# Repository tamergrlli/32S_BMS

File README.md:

# 32S BMS

A battery management system board for **16S to 32S** packs, built around two
stacked **TI BQ76952** monitors and an **STM32G0B1** microcontroller. Designed in
KiCad 10.

| | |
|---|---|
| Cell count | 16S to 32S (2 × BQ76952, up to 16 cells each) |
| Balancing | 32 external MOSFET balancing channels |
| Supply | 12 V nominal (see [Power](#power)) |
| Interfaces | CAN, 4 high-side outputs, 6 configurable inputs |
| Board | 90 × 100 mm, 4 copper layers, 1.6 mm |
| Parts | 413 footprints |
| Revision | V0.1 |

## Features

### Cell monitoring and balancing
- Two BQ76952 monitors (`bq76952_TOP` / `bq76952_BOTTOM`) stacked to cover up to
  32 cells. The cell count is configurable between 16S and 32S.
- 32 external balancing channels (AO3416 MOSFETs with 2512 bleed resistors) with
  zener gate protection.
- Cell sense inputs on two Molex Micro-Fit 3.0 2×10 connectors.

### Isolation
- Each monitor has its own isolated link to the MCU. An ISO1644 carries I²C, ALERT
  and SHUT, and a PC817 optocoupler drives WAKE.

### Inputs
- 6 input channels on one connector, multiplexed through a 74HC4051 into a single
  MCU ADC channel.
- Each channel has a 4.7 kΩ series resistor, a 10 kΩ pull-down and a 100 nF filter
  capacitor. The connector also provides a 3.3 V pin through a 47 Ω resistor.
- Because of this structure, the same input can read either an analog or a digital
  signal:
  - **NTC thermistor** between the 3.3 V pin and the input forms a divider with
    the on-board resistors.
  - **Button or switch** to 3.3 V reads high when closed and is held low by the
    pull-down when open.
  - **Analog voltage** up to about 4.8 V full scale, set by the 4.7 k / 10 k
    divider.
- On-board NTC for board temperature.

### Always-on operation and sleep on command
- The BMS runs continuously and enters sleep mode only on command, for example
  from a CAN message.
- A TPL5010 nano-power timer acts as an external watchdog. The MCU acknowledges it
  periodically, and if the firmware hangs, the TPL5010 resets the MCU. The reset
  output reaches NRST through a jumper, so the watchdog can be disabled.
- In sleep mode, the MCU can put each BQ76952 into SHUTDOWN and the CAN transceiver
  into standby. Wake sources:
  - CAN bus activity
  - a push button, through the TPL5010 manual-reset input
  - a BQ76952 ALERT

### Communication and outputs
- CAN bus with a TJA1042T/3 transceiver, TDK ACT45B common-mode choke and
  PESD1CAN ESD protection. 120 Ω termination is selectable by jumper.
- 4 high-side switched outputs (Infineon BTS724G) at supply voltage, with
  flyback diodes and status feedback to the MCU.

### MCU and peripherals
- STM32G0B1RE with an external main crystal and a 32.768 kHz RTC crystal. The
  RTC is backed up by a CR1220 coin cell.
- W25Q32 SPI flash (32 Mbit) for data logging.
- SWD header, two status LEDs, a buzzer and a push button.

### Power
- 12 V input, protected by:
  - a fuse
  - an SS34 series diode for reverse polarity on the logic supply
  - an SMAJ15CA TVS diode
  - a P-MOSFET with zener-clamped gate for reverse polarity on the output stage
- A TPS54302 buck converter makes 5 V, and an AP2112K LDO makes 3.3 V.
- **Supply range:** 12 V nominal.
  - The upper limit is set by the SMAJ15CA TVS: 15 V standoff, about 16.7 V
    breakdown.
  - At the low end, the 5 V buck plus the series diode drop need roughly 6–7 V.
  - The TPS54302 itself accepts 4.5–28 V, so the input protection is what limits
    the range.

## Firmware

Firmware is under development and will be published in this repository as it
progresses.

## Gallery

| Top | Bottom |
|---|---|
|  |  |

## Repository layout

```
32s_bms/        KiCad project (schematic sheets: POWER, IN_OUT, MCU, bq76952)
32s_bms_lib/    Every non-standard part used by the design
  symbols/      Custom schematic symbols
  footprints/   Custom footprint libraries (.pretty)
  3dmodels/     STEP models for connectors and custom parts
32s_gerber/     Gerber and drill files (exported 2026-10-12)
32s_pdf/        Schematic PDF
docs/           Renders
```

## Opening the project

1. Install [KiCad 10](https://www.kicad.org/download/).
2. Clone the repository and open `32s_bms/32s_bms.kicad_pro`.

All custom symbols, footprints and 3D models are included, and the project
library tables use `${KIPRJMOD}`-relative paths. You don't need to configure any
libraries. Everything else comes from KiCad's standard libraries.

## Notes

- This is revision V0.1, shared as a design reference. Battery packs at this
  series count carry hazardous voltages. Review and test the design yourself
  before using it with real cells.
- Third-party 3D models (Molex, JST, TDK, Panasonic and others) are the property
  of their manufacturers and are included only so the 3D view renders correctly.

## License

The design files are released under the [MIT License](LICENSE). Third-party 3D
models in `32s_bms_lib/3dmodels/` are not covered by this license and remain under
their manufacturers' terms.

## Author

Tamer Gürelli

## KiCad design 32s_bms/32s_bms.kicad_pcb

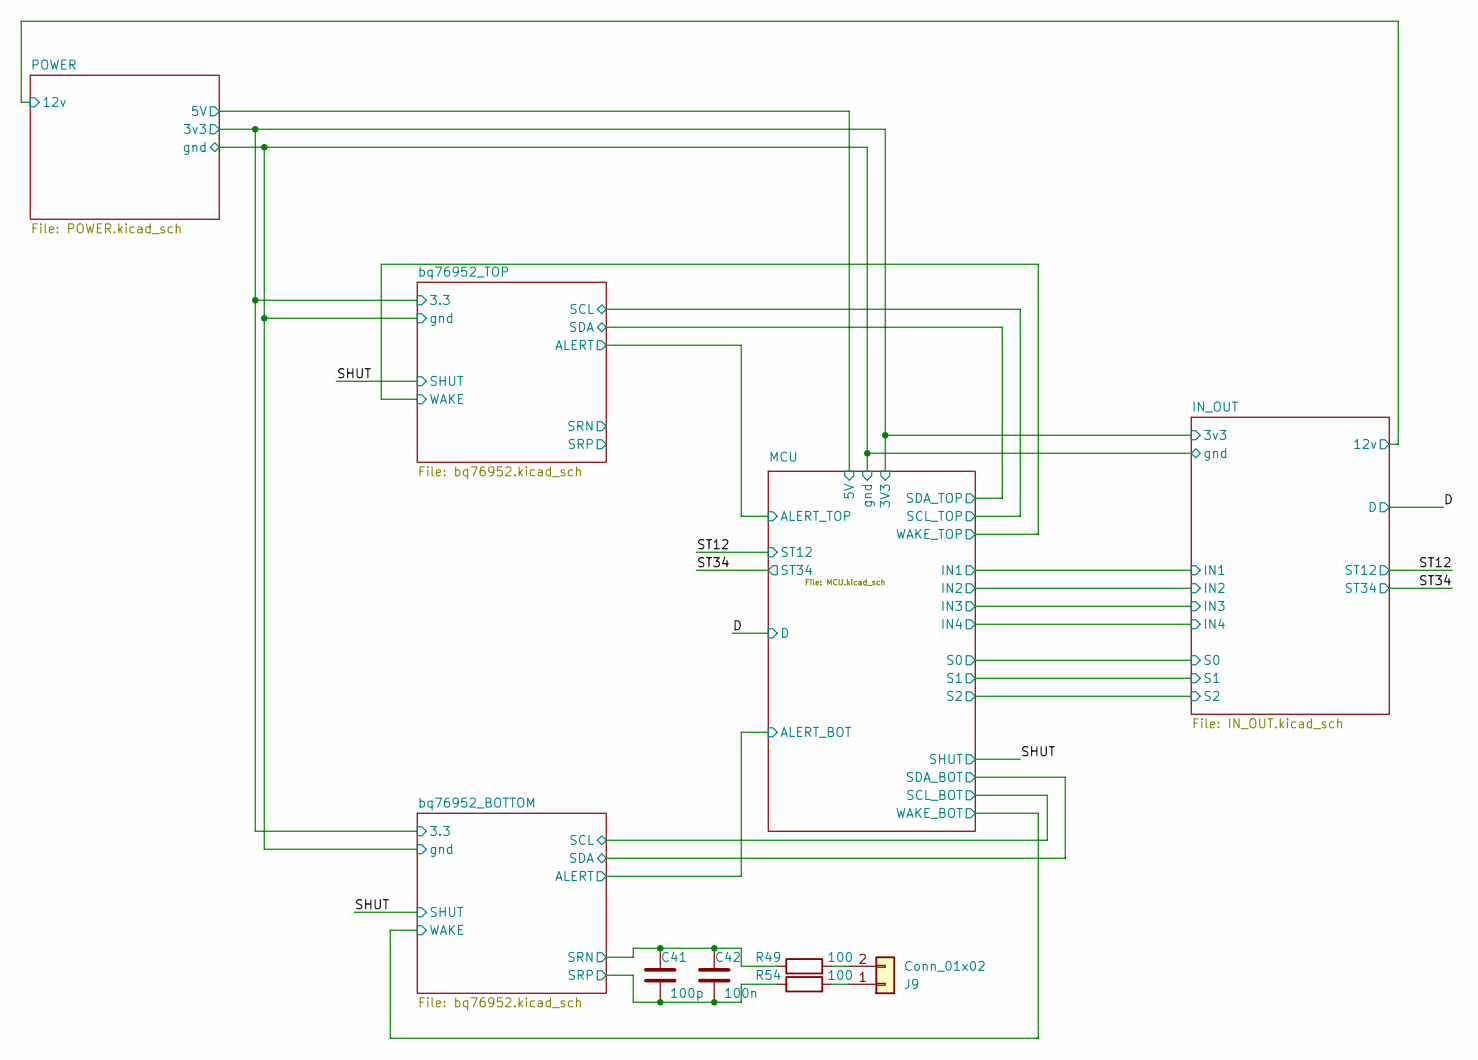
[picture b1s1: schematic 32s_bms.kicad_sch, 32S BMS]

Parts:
C41: 100p; C_0603_1608Metric
C42: 100n; C_0603_1608Metric
J9: Conn_01x02; JST_PH_S2B-PH-SM4-TB_1x02-1MP_P2.00mm_Horizontal
R49, R54: 100; R_0603_1608Metric

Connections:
/bq76952_BOTTOM/SRN: C41.2, C42.2, R49.1; also elsewhere on the board
/bq76952_BOTTOM/SRP: C41.1, C42.1, R54.1; also elsewhere on the board
unnamed: J9.1, R54.2
unnamed: J9.2, R49.2

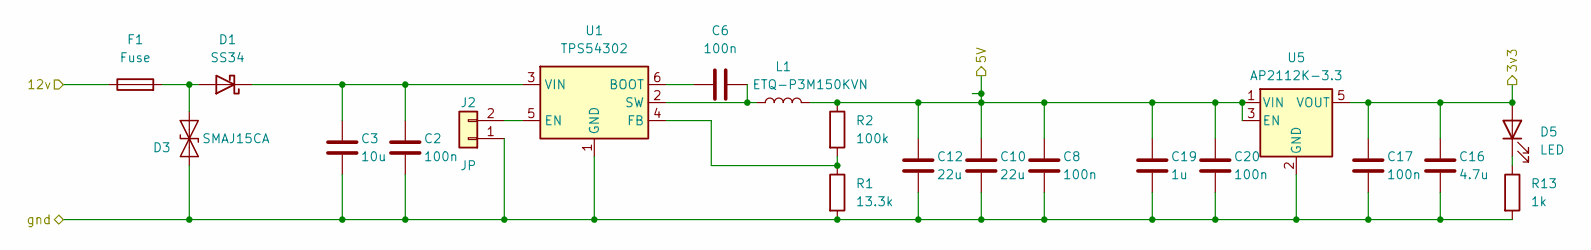
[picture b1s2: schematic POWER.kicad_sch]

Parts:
C2, C6, C8, C17, C20: 100n; C_0603_1608Metric
C3: 10u; C_1206_3216Metric
C10, C12: 22u; C_1206_3216Metric
C16: 4.7u; C_1206_3216Metric
C19: 1u; C_0805_2012Metric
D1: SS34; D_SMA
D3: SMAJ15CA; D_SMA
D5: LED; LED_0805_2012Metric
F1: Fuse; Fuse_1206_3216Metric
J2: JP; PinHeader_1x02_P1.27mm_Vertical
L1: ETQ-P3M150KVN; L_Panasonic_PCC-M0630M
R1: 13.3k; R_0603_1608Metric
R2: 100k; R_0603_1608Metric
R13: 1k; R_0603_1608Metric
U1: TPS54302; SOT-23-6
U5: AP2112K-3.3; SOT-23-5

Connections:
/IN_OUT/3v3: C16.1, C17.2, D5.2 (A), U5.5 (VOUT); also elsewhere on the board
/IN_OUT/12v: F1.1; also elsewhere on the board
/IN_OUT/gnd: C2.1, C3.2, C8.1, C10.2, C12.2, C16.2, C17.1, C19.2, C20.1, D3.2 (A2), J2.1, R1.2, R13.2, U1.1 (GND), U5.2 (GND); also elsewhere on the board
/MCU/5V: C8.2, C10.1, C12.1, C19.1, C20.2, L1.2, R2.1, U5.1 (VIN), U5.3 (EN); also elsewhere on the board
unnamed: D1.2 (A), D3.1 (A1), F1.2
unnamed: C2.2, C3.1, D1.1 (K), U1.3 (VIN)
unnamed: D5.1 (K), R13.1
unnamed: J2.2, U1.5 (EN)
unnamed: C6.1, U1.6 (BOOT)
unnamed: R1.1, R2.2, U1.4 (FB)
unnamed: C6.2, L1.1, U1.2 (SW)

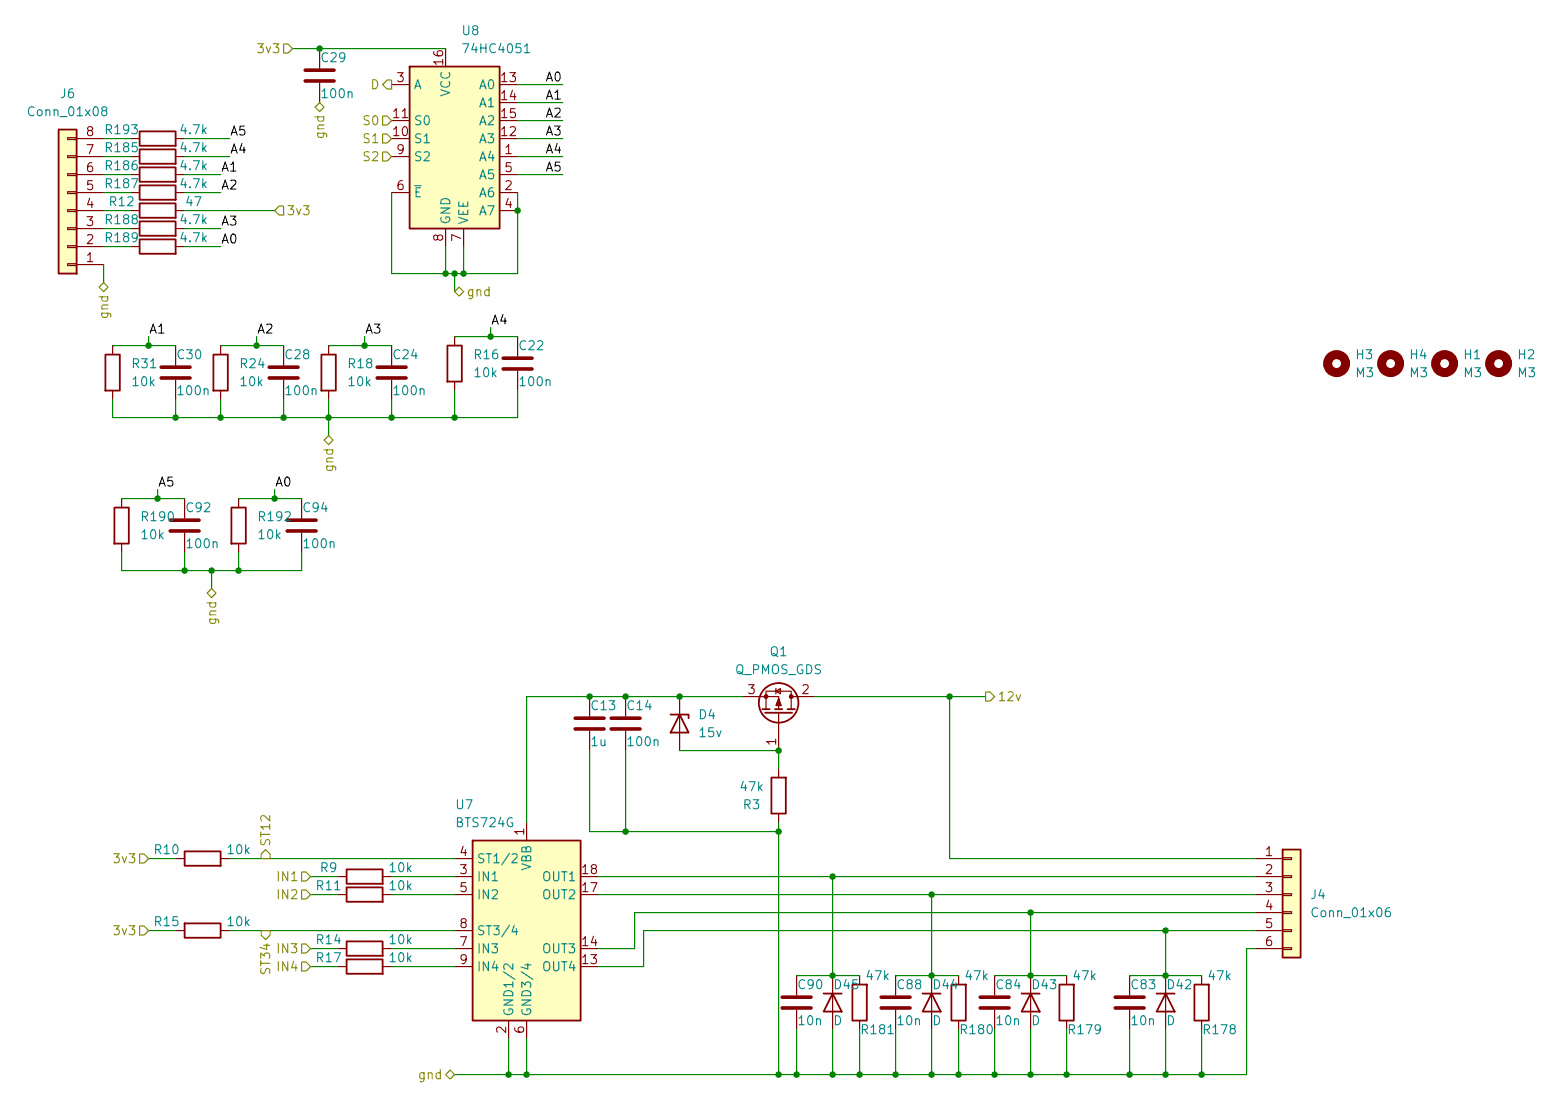
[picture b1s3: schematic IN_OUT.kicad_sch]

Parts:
C13: 1u; C_0805_2012Metric
C14, C22, C24, C28, C29, C30, C92, C94: 100n; C_0603_1608Metric
C83, C84, C88, C90: 10n; C_0805_2012Metric
D4: 15v; D_SOD-123
D42, D43, D44, D45: D; D_SOD-123
H1, H2, H3, H4: M3; MountingHole_3.2mm_M3
J4: Conn_01x06; Molex_Micro-Fit_3.0_43650-0600_1x06_P3.00mm_Horizontal
J6: Conn_01x08; Molex_Micro-Fit_3.0_43045-0800_2x04_P3.00mm_Horizontal
Q1: Q_PMOS_GDS; TO-252-2
R3, R178, R179, R180, R181: 47k; R_0805_2012Metric
R9, R10, R11, R14, R15, R16, R17, R18, R24, R31, R190, R192: 10k; R_0603_1608Metric
R12: 47; R_0805_2012Metric
R185, R186, R187, R188, R189, R193: 4.7k; R_0603_1608Metric
U7: BTS724G; Infineon_SOIC-20W_7.6x12.8mm_P1.27mm
U8: 74HC4051; TSSOP-16_4.4x5mm_P0.65mm

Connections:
/D: U8.3 (A); also elsewhere on the board
/IN_OUT/3v3: C29.1, R10.1, R12.2, R15.2, U8.16 (VCC); also elsewhere on the board
/IN_OUT/12v: J4.1, Q1.2 (D); also elsewhere on the board
/IN_OUT/A0: C94.1, R189.2, R192.1, U8.13 (A0)
/IN_OUT/A1: C30.1, R31.1, R186.2, U8.14 (A1)
/IN_OUT/A2: C28.1, R24.1, R187.2, U8.15 (A2)
/IN_OUT/A3: C24.1, R18.1, R188.2, U8.12 (A3)
/IN_OUT/A4: C22.1, R16.1, R185.2, U8.1 (A4)
/IN_OUT/A5: C92.1, R190.1, R193.2, U8.5 (A5)
/IN_OUT/IN1: R9.1; also elsewhere on the board
/IN_OUT/IN2: R11.1; also elsewhere on the board
/IN_OUT/IN3: R14.1; also elsewhere on the board
/IN_OUT/IN4: R17.1; also elsewhere on the board
/IN_OUT/S0: U8.11 (S0); also elsewhere on the board
/IN_OUT/S1: U8.10 (S1); also elsewhere on the board
/IN_OUT/S2: U8.9 (S2); also elsewhere on the board
/IN_OUT/gnd: C13.2, C14.2, C22.2, C24.2, C28.2, C29.2, C30.2, C83.2, C84.2, C88.2, C90.2, C92.2, C94.2, D42.2 (A), D43.2 (A), D44.2 (A), D45.2 (A), J4.6, J6.1, R3.1, R16.2, R18.2, R24.2, R31.2, R178.1, R179.1, R180.1, R181.1, R190.2, R192.2, U7.2 (GND1/2), U7.6 (GND3/4), U8.2 (A6), U8.4 (A7), U8.6 (~E), U8.7 (VEE), U8.8 (GND); also elsewhere on the board
/ST12: R10.2, U7.4 (ST1/2); also elsewhere on the board
/ST34: R15.1, U7.8 (ST3/4); also elsewhere on the board
unnamed: D4.2 (A), Q1.1 (G), R3.2
unnamed: C13.1, C14.1, D4.1 (K), Q1.3 (S), U7.1 (VBB), U7.10 (VBB), U7.11 (VBB), U7.12 (VBB), U7.15 (VBB), U7.16 (VBB), U7.19 (VBB), U7.20 (VBB)
unnamed: C83.1, D42.1 (K), J4.5, R178.2, U7.13 (OUT4)
unnamed: C84.1, D43.1 (K), J4.4, R179.2, U7.14 (OUT3)
unnamed: C88.1, D44.1 (K), J4.3, R180.2, U7.17 (OUT2)
unnamed: C90.1, D45.1 (K), J4.2, R181.2, U7.18 (OUT1)
unnamed: J6.2, R189.1
unnamed: J6.3, R188.1
unnamed: J6.4, R12.1
unnamed: J6.5, R187.1
unnamed: J6.6, R186.1
unnamed: J6.7, R185.1
unnamed: J6.8, R193.1
unnamed: R9.2, U7.3 (IN1)
unnamed: R11.2, U7.5 (IN2)
unnamed: R14.2, U7.7 (IN3)
unnamed: R17.2, U7.9 (IN4)

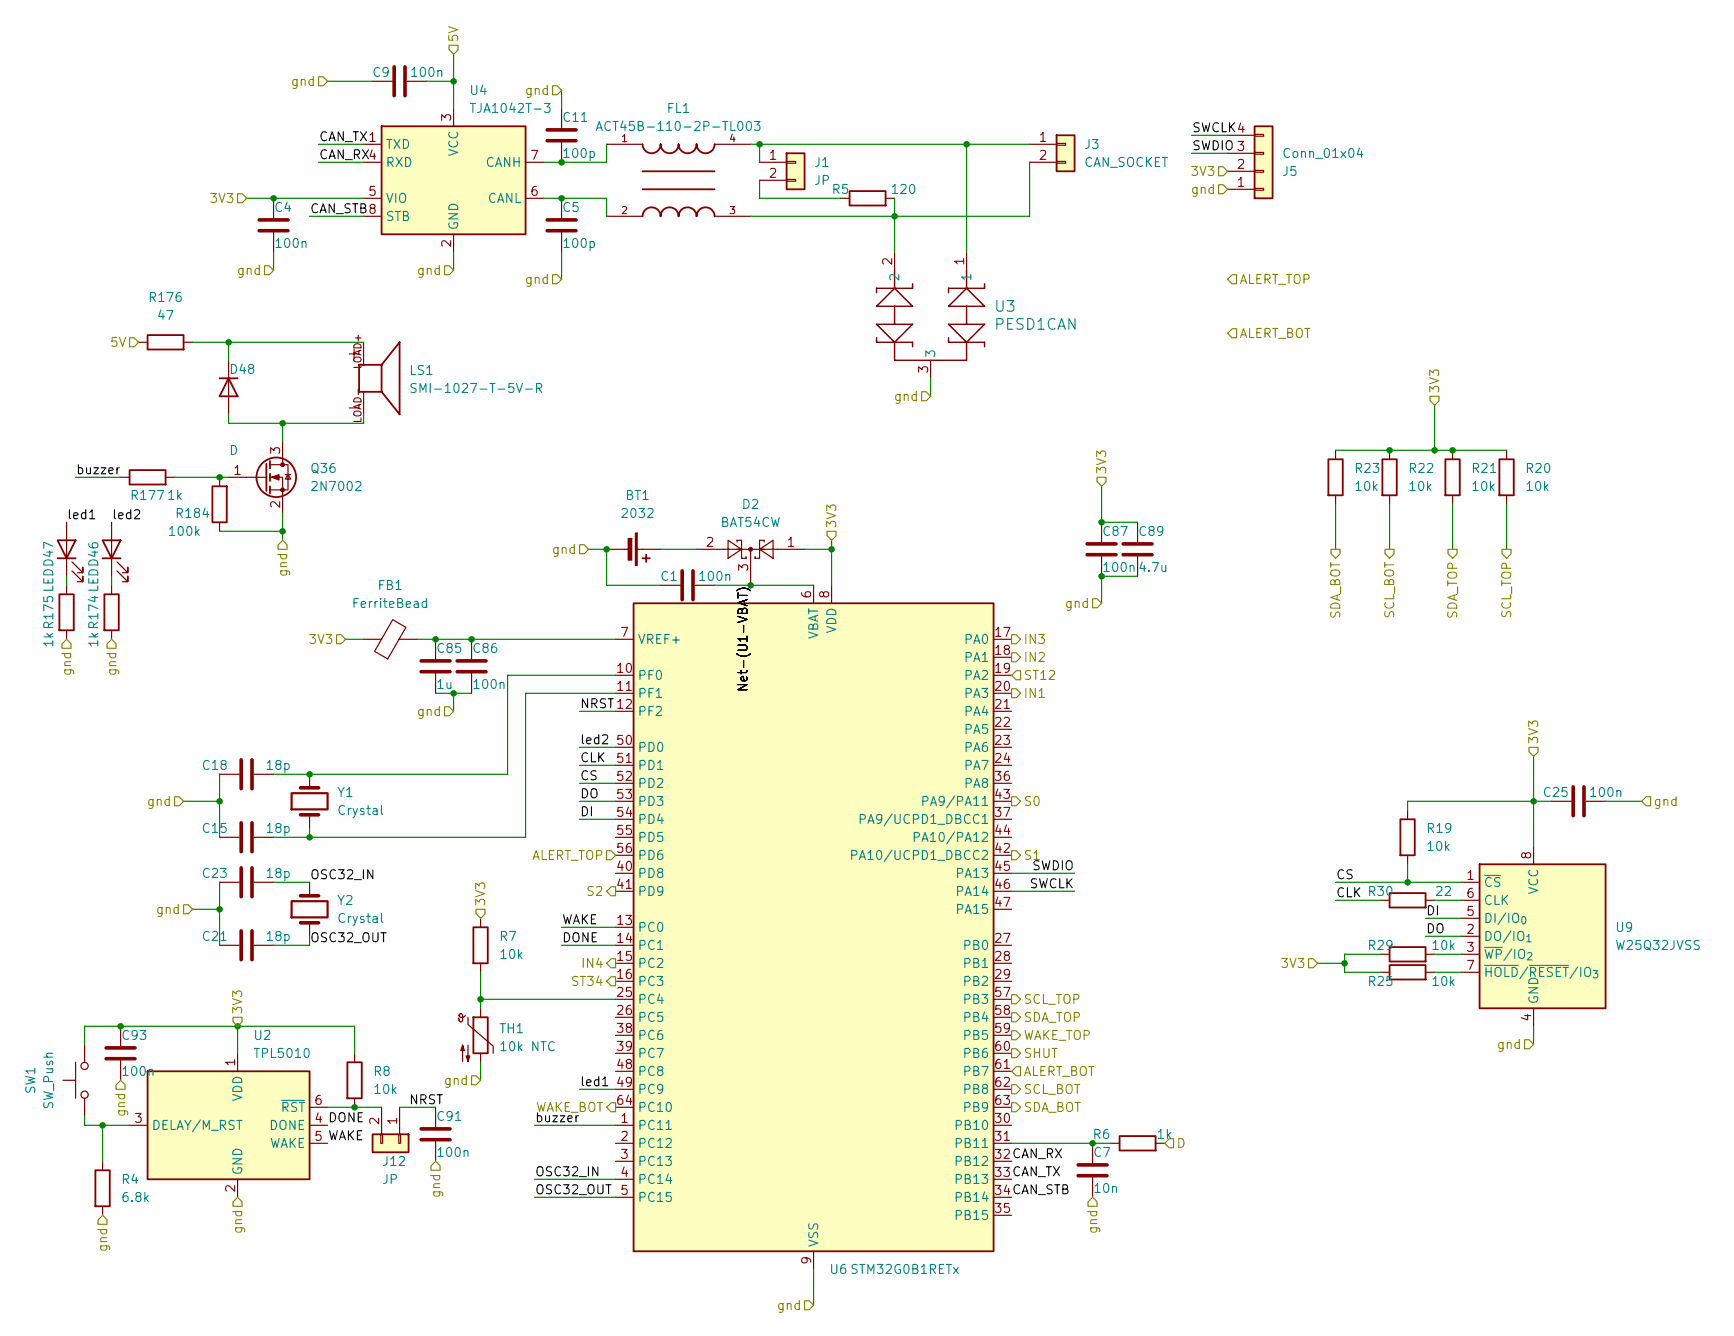
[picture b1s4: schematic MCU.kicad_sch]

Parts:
BT1: 2032; Battery_Panasonic_CR1220-VCN_Vertical_CircularHoles
C1, C4, C9, C25, C86, C87, C91, C93: 100n; C_0603_1608Metric
C5, C11: 100p; C_0603_1608Metric
C7: 10n; C_0805_2012Metric
C15, C18, C21, C23: 18p; C_0603_1608Metric
C85: 1u; C_0805_2012Metric
C89: 4.7u; C_1206_3216Metric
D2: BAT54CW; SOT-323_SC-70
D46, D47: LED; LED_0805_2012Metric
D48: D; D_SOD-123
FB1: FerriteBead; L_0603_1608Metric
FL1: ACT45B-110-2P-TL003; PARTREV 20200405
J1, J12: JP; PinHeader_1x02_P1.27mm_Vertical
J3: CAN_SOCKET; Molex_Micro-Fit_3.0_43650-0200_1x02_P3.00mm_Horizontal
J5: Conn_01x04; PinHeader_1x04_P2.54mm_Vertical
LS1: SMI-1027-T-5V-R; XDCR_SMI-1027-T-5V-R; PARTREV 03/26/2020; DigiKey_Part_Number 668-SMI-1027-T-5V-RCT-ND
Q36: 2N7002; SOT-23
R4: 6.8k; R_0603_1608Metric
R5: 120; R_0603_1608Metric
R6, R174, R175, R177: 1k; R_0603_1608Metric
R7, R8, R19, R20, R21, R22, R23, R25, R29: 10k; R_0603_1608Metric
R30: 22; R_0805_2012Metric
R176: 47; R_0805_2012Metric
R184: 100k; R_0603_1608Metric
SW1: SW_Push; SW_Push_1P1T_NO_CK_KMR2
TH1: 10k NTC; R_0805_2012Metric
U2: TPL5010; SOT-23-6
U3: PESD1CAN; SOT23_NXP
U4: TJA1042T-3; SOIC-8_3.9x4.9mm_P1.27mm
U6: STM32G0B1RETx; LQFP-64_10x10mm_P0.5mm
U9: W25Q32JVSS; SOIC-8_5.3x5.3mm_P1.27mm
Y1: Crystal; Crystal_SMD_5032-2Pin_5.0x3.2mm
Y2: Crystal; Crystal_SMD_3215-2Pin_3.2x1.5mm

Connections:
/D: R6.2; also elsewhere on the board
/IN_OUT/3v3: C4.1, C25.1, C87.1, C89.1, C93.1, D2.1, FB1.1, J5.2, R7.1, R8.1, R19.1, R20.1, R21.1, R22.1, R23.1, R25.1, R29.1, SW1.2, U2.1 (VDD), U4.5 (VIO), U6.8 (VDD), U9.8 (VCC); also elsewhere on the board
/IN_OUT/IN1: U6.20 (PA3); also elsewhere on the board
/IN_OUT/IN2: U6.18 (PA1); also elsewhere on the board
/IN_OUT/IN3: U6.17 (PA0); also elsewhere on the board
/IN_OUT/IN4: U6.15 (PC2); also elsewhere on the board
/IN_OUT/S0: U6.43 (PA9/PA11); also elsewhere on the board
/IN_OUT/S1: U6.42 (PA10/UCPD1_DBCC2); also elsewhere on the board
/IN_OUT/S2: U6.41 (PD9); also elsewhere on the board
/IN_OUT/gnd: BT1.2 (-), C1.1, C4.2, C5.2, C7.2, C9.1, C11.1, C15.1, C18.1, C21.1, C23.1, C25.2, C85.2, C86.2, C87.2, C89.2, C91.2, C93.2, J5.1, Q36.2 (S), R4.2, R174.2, R175.2, R184.1, TH1.2, U2.2 (GND), U3.3, U4.2 (GND), U6.9 (VSS), U9.4 (GND); also elsewhere on the board
/MCU/5V: C9.2, R176.1, U4.3 (VCC); also elsewhere on the board
/MCU/ALERT_BOT: U6.61 (PB7); also elsewhere on the board
/MCU/ALERT_TOP: U6.56 (PD6); also elsewhere on the board
/MCU/CAN_RX: U4.4 (RXD), U6.32 (PB12)
/MCU/CAN_STB: U4.8 (STB), U6.34 (PB14)
/MCU/CAN_TX: U4.1 (TXD), U6.33 (PB13)
/MCU/CLK: R30.1, U6.51 (PD1)
/MCU/CS: R19.2, U6.52 (PD2), U9.1 (~CS)
/MCU/DI: U6.54 (PD4), U9.5 (DI/IO_{0})
/MCU/DO: U6.53 (PD3), U9.2 (DO/IO_{1})
/MCU/DONE: U2.4 (DONE), U6.14 (PC1)
/MCU/NRST: C91.1, J12.1, U6.12 (PF2)
/MCU/Net-(U1-VBAT): C1.2, D2.3, U6.6 (VBAT)
/MCU/OSC32_IN: C23.2, U6.4 (PC14), Y2.2
/MCU/OSC32_OUT: C21.2, U6.5 (PC15), Y2.1
/MCU/SCL_BOT: R22.2, U6.62 (PB8); also elsewhere on the board
/MCU/SCL_TOP: R20.2, U6.57 (PB3); also elsewhere on the board
/MCU/SDA_BOT: R23.2, U6.63 (PB9); also elsewhere on the board
/MCU/SDA_TOP: R21.2, U6.58 (PB4); also elsewhere on the board
/MCU/SWCLK: J5.4, U6.46 (PA14)
/MCU/SWDIO: J5.3, U6.45 (PA13)
/MCU/WAKE: U2.5 (WAKE), U6.13 (PC0)
/MCU/WAKE_BOT: U6.64 (PC10); also elsewhere on the board
/MCU/WAKE_TOP: U6.59 (PB5); also elsewhere on the board
/MCU/buzzer: R177.1, U6.1 (PC11)
/MCU/led1: D47.2 (A), U6.49 (PC9)
/MCU/led2: D46.2 (A), U6.50 (PD0)
/SHUT: U6.60 (PB6); also elsewhere on the board
/ST12: U6.19 (PA2); also elsewhere on the board
/ST34: U6.16 (PC3); also elsewhere on the board
unnamed: BT1.1 (+), D2.2
unnamed: D46.1 (K), R174.1
unnamed: D47.1 (K), R175.1
unnamed: D48.2 (A), LS1.LOAD-, Q36.3 (D)
unnamed: D48.1 (K), LS1.LOAD+, R176.2
unnamed: FL1.4, J1.1, J3.1, U3.1
unnamed: J1.2, R5.1
unnamed: FL1.3, J3.2, R5.2, U3.2
unnamed: J12.2, R8.2, U2.6 (~RST)
unnamed: Q36.1 (G), R177.2, R184.2
unnamed: R4.1, SW1.1, U2.3 (DELAY/M_RST)
unnamed: C11.2, FL1.1, U4.7 (CANH)
unnamed: C5.1, FL1.2, U4.6 (CANL)
unnamed: C7.1, R6.1, U6.31 (PB11)
unnamed: R7.2, TH1.1, U6.25 (PC4)
unnamed: C18.2, U6.10 (PF0), Y1.2
unnamed: C15.2, U6.11 (PF1), Y1.1
unnamed: C85.1, C86.1, FB1.2, U6.7 (VREF+)
unnamed: R30.2, U9.6 (CLK)
unnamed: R25.2, U9.7 (~HOLD/~RESET/IO_{3})
unnamed: R29.2, U9.3 (~WP/IO_{2})
